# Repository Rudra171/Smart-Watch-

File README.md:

# Smart-Watch-

# SmartWatch Project

## Overview

Welcome to the SmartWatch project! This repository contains the documentation for a smartwatch designed to track the heartrate,bodytemperature, and body steps.

## Features

- **Heart Rate Monitoring:** Keep tabs on your heart health with real-time heart rate monitoring.
- **Body Temperature Tracking:** Monitor your body temperature to stay aware of changes in your health.
- **Step Counter:** Track your daily steps and stay motivated to achieve your fitness goals.

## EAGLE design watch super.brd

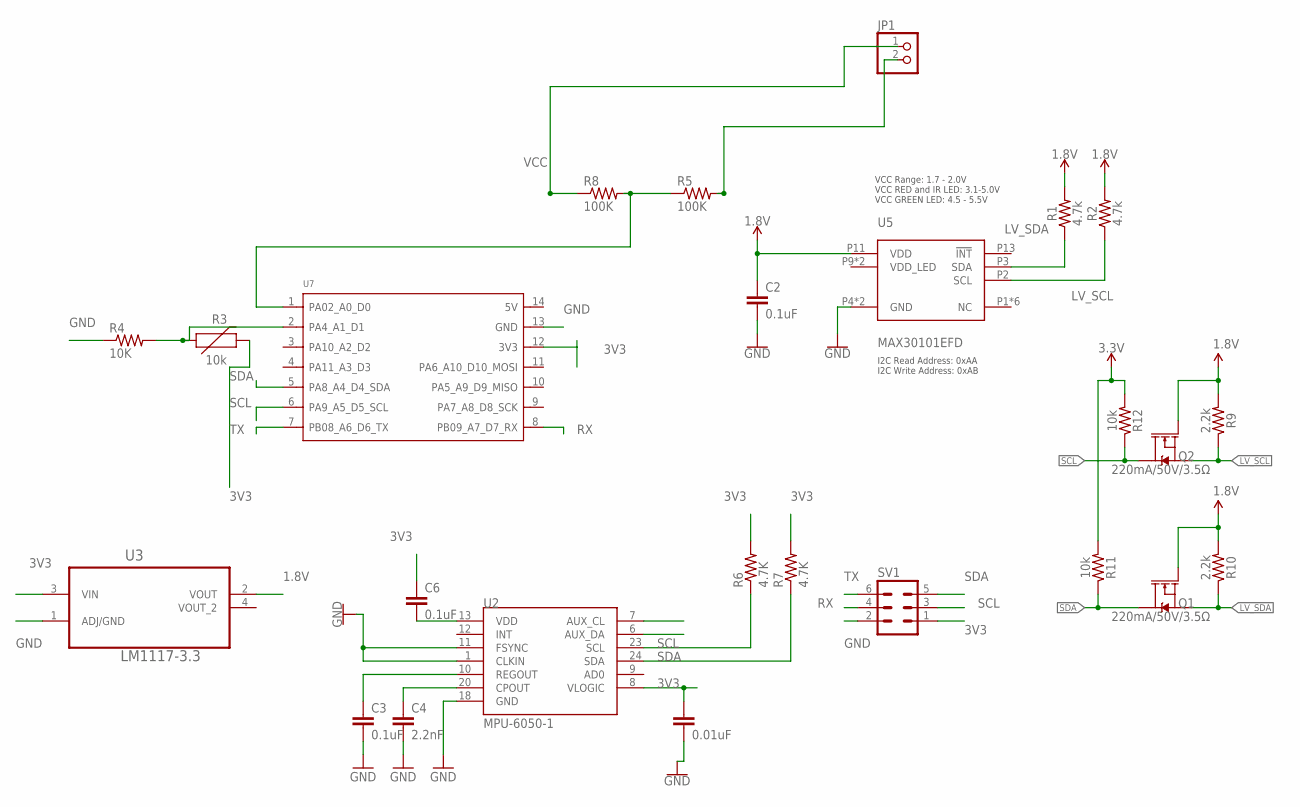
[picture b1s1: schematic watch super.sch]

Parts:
0.01UF: 0.01uF; 0603-CAP
C2: 0.1uF; 0402
C3, C6: 0.1uF; 0603-CAP
C4: 2.2nF; 0603-CAP
JP1: PINHD-1X2; 1X02
Q1, Q2: 220mA/50V/3.5Ω; SOT23-3
R1, R2: 4.7k; 0603
R3: 10k; 0603@1
R4: 10K; M1206
R5, R8: 100K; R0603
R6, R7: 4.7K; 0603-RES
R9, R10: 2.2k; 0603
R11, R12: 10k; 0603
SV1: MA03-2
U2: MPU-6050-1; QFN-24-4MM2
U3: LM1117-3.3; SOT230
U5: MAX30101EFD; 14_PIN_OESIP
U7: SEEEDUINOTHT; MOUDLE14P-2.54-21X17.8MM

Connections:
1.8V: C2.1, Q1.1 (G), Q2.1 (G), R1.2, R2.2, R9.2, R10.2, U3.2 (VOUT), U5.P11 (VDD)
3.3V: R11.2, R12.2
3V3: 0.01UF.1, C6.1, R3.2, R6.2, R7.2, SV1.1, U2.8 (VLOGIC), U3.3 (VIN), U7.12 (3V3)
AUX_SCL: U2.7 (AUX_CL)
AUX_SDA: U2.6 (AUX_DA)
GND: 0.01UF.2, C2.2, C3.2, C4.2, R4.1, SV1.2, U2.1 (CLKIN), U2.11 (FSYNC), U2.18 (GND), U3.1 (ADJ/GND), U5.P4 (GND), U5.P12 (GND), U7.13 (GND)
LV_SCL: Q2.2 (S), R2.1, R9.1, U5.P2 (SCL)
LV_SDA: Q1.2 (S), R1.1, R10.1, U5.P3 (SDA)
unnamed: R3.1, R4.2, U7.2 (PA4_A1_D1)
unnamed: JP1.2, R5.2
unnamed: C4.1, U2.20 (CPOUT)
unnamed: C3.1, U2.10 (REGOUT)
unnamed: C6.2, U2.13 (VDD)
unnamed: R5.1, R8.2, U7.1 (PA02_A0_D0)
RX: SV1.4, U7.8 (PB09_A7_D7_RX)
SCL: Q2.3 (D), R6.1, R12.1, SV1.3, U2.23 (SCL), U7.6 (PA9_A5_D5_SCL)
SDA: Q1.3 (D), R7.1, R11.1, SV1.5, U2.24 (SDA), U7.5 (PA8_A4_D4_SDA)
TX: SV1.6, U7.7 (PB08_A6_D6_TX)
VCC: JP1.1, R8.1
VDD_LED: U5.P9 (VDD_LED), U5.P10 (VDD_LED)

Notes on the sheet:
VCC Range: 1.7 - 2.0V VCC RED and IR LED: 3.1-5.0V VCC GREEN LED: 4.5 - 5.5V
I2C Read Address: 0xAA I2C Write Address: 0xAB

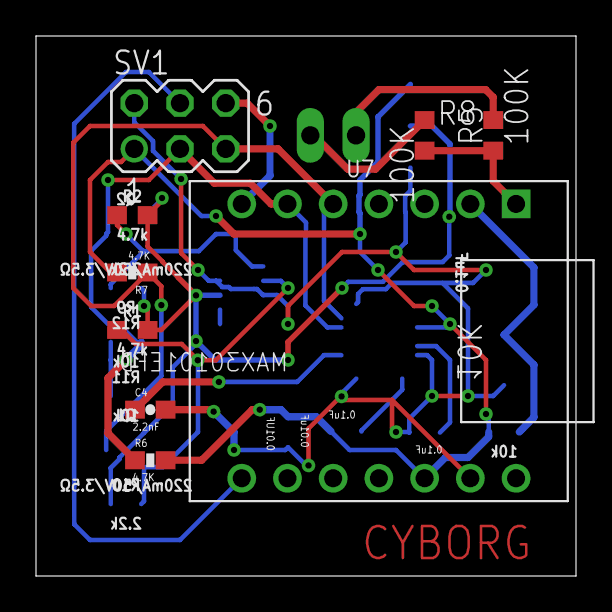
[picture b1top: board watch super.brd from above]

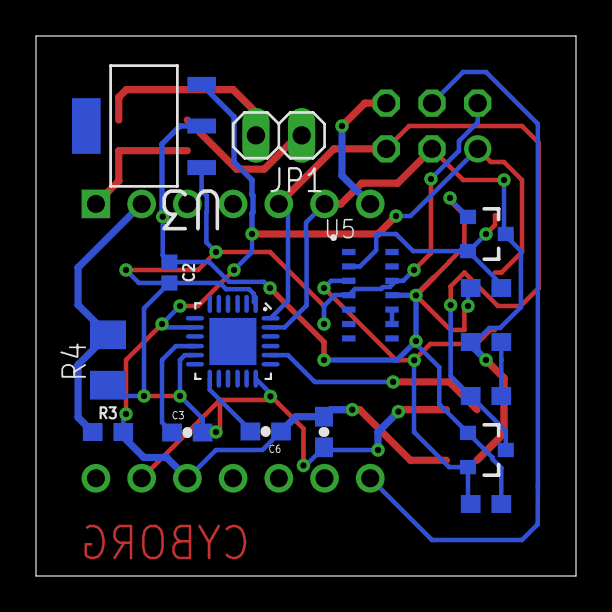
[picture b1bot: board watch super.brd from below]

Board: 2 copper layers, 30.0 x 30.0 mm, 25 parts (16 on the bottom side), 18 nets.

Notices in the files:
parts and their libraries:
SparkFun-Capacitors: Licensing: Creative Commons ShareAlike 4.0 International - https://creativecommons.org/licenses/by-sa/4.0
SparkFun-Aesthetics: Licensing: CC v3.0 Share-Alike You are welcome to use this library for commercial purposes.
